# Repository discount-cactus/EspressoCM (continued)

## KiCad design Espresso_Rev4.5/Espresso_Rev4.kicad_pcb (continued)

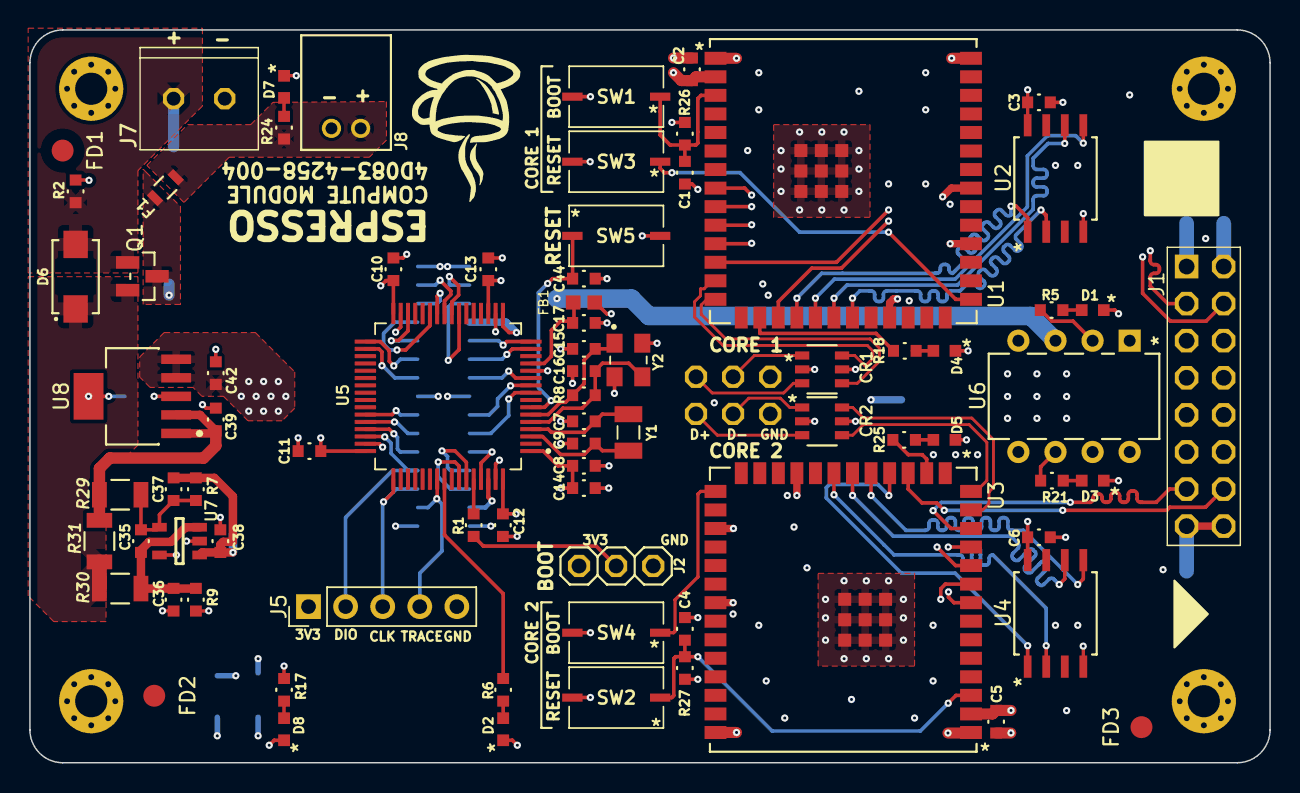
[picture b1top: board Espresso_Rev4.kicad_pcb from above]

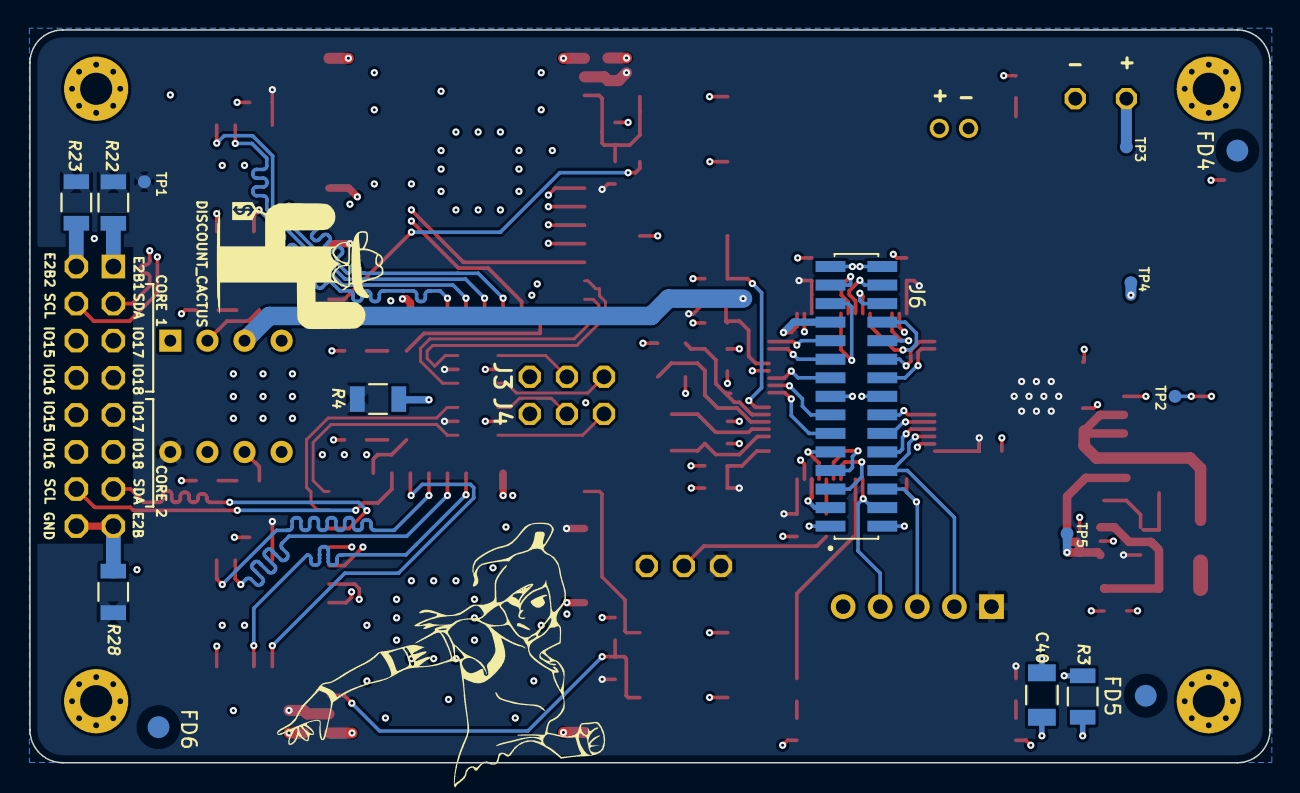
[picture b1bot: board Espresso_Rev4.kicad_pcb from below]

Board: 4 copper layers, 84.9 x 50.2 mm, 98 parts (15 on the bottom side), 89 nets.

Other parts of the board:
MH1, MH2, MH3, MH4: MountingHole_2.2mm_M2_Pad_Via

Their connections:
/SHIELD: MH1.1, MH2.1, MH3.1, MH4.1; also elsewhere on the board

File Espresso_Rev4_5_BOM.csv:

"#","Reference","Qty","Value","Footprint","Manufacturer","Part Number","Alt Part Number","Rating","Color","DNP","Voltage Rating"
"1","C14","1","4.7uF","Custom_Microcontroller:C_0603","Samsung","CL10A475MA8NQNC","","25V","","",""
"2","C40","1","4.7nF","Custom_Microcontroller:C_1206","KEMET","C1206C472KDRACAUTO","","1kV","","DNP",""
"3","C1,C4","2","1uF","Custom_Microcontroller:C_0603","Samsung","CL10A105KB8NNNC","","50V","","",""
"4","C15,C16","2","20pF","Custom_Microcontroller:C_0603","Samsung","CL10C200JB8NNNC","","50V","","",""
"5","C2,C3,C5,C6,C8,C10,C11,C12,C13,C17,C38,C44","12","100nF","Custom_Microcontroller:C_0603","Samsung","CL10B104KB8NNNC","","50V","","",""
"6","C35,C36,C37","3","220pF","Custom_Microcontroller:C_0603","Samsung","CL10B221KB8NFNC","C0603C221J5HACAUTO","50V","","",""
"7","C39,C42","2","10uF","Custom_Microcontroller:C_0603","Samsung","CL10A106MA8NRNC","","25V","","",""
"8","C7,C9","2","8pF","Custom_Microcontroller:C_0603","Samsung","CL10C080DB81PNC","","50V","","DNP",""
"9","CR1,CR2","2","USBLC6-2SC6","Custom_Microcontroller:USBLC6-2SC6","STMicroelectronics","USBLC6-2SC6","","","","",""
"10","D6","1","~","Custom_Microcontroller:SK54AHE3-LTP","MCC","SK54AHE3-LTP","","","","",""
"11","D1,D4,D5","3","~","Custom_Microcontroller:LED_0603","Lite-On Inc.","LTST-C191KGKT","","","Green","",""
"12","D2,D3,D7,D8","4","~","Custom_Microcontroller:LED_0603","Lite-On Inc.","LTST-C191KFKT","","","Orange","",""
"13","F1","1","1A","Custom_Microcontroller:MF-FSMF050X-2","Bourns","MF-FSMF050X-2 ","","","","",""
"14","FB1","1","120R","Custom_Microcontroller:FB_0603","Murata","BLM18KG121TN1D","","","","",""
"15","J1","1","~","Custom_Microcontroller:2X8","Sullins","PPTC082LJBN-RC","","","","",""
"16","J5","1","Conn_01x05","Connector_PinHeader_2.54mm:PinHeader_1x05_P2.54mm_Vertical","","","","","","",""
"17","J6","1","20021321-00030T4LF","Custom_Microcontroller:20021321-00030T4LF","Amphenol","20021321-00030T4LF","","","","",""
"18","J7","1","OSTTE020104","Custom_Microcontroller:OSTTE020104","On Shore Technology","OSTTE020104","","10A","","",""
"19","J8","1","S2B-PH-K-S","Custom_Microcontroller:S2B-PH-K-S","JST","S2B-PH-K-S","","","","",""
"20","J2,J3,J4","3","~","Custom_Microcontroller:1X3","","","","","","",""
"21","Q1","1","~","Custom_Microcontroller:DMP3099L-7","Diodes","DMP3099L-7","","","","",""
"22","R2","1","100K","Custom_Microcontroller:R_0603","Stackpole","RMCF0603FT100K","","1/10W","","",""
"23","R3","1","1M00","Custom_Microcontroller:R_1206","Stackpole","RMCF1206FG1M00","","1/4W","","DNP",""
"24","R8","1","1M00","Custom_Microcontroller:R_0603","Stackpole","RMCF0603FT1M00","","1/10W","","",""
"25","R31","1","3mOhm","Custom_Microcontroller:R_1206","Rohm Semiconductor","PMR18EZPFV3L00","","1W","","",""
"26","R1,R26,R27","3","10K","Custom_Microcontroller:R_0603","Stackpole","RMCF0603FT10K0","","1/10W","","",""
"27","R29,R30","2","97R6","Custom_Microcontroller:R_1206","KOA Speer","RK73H2BTTD97R6F","","1/4W","","",""
"28","R4,R22,R23,R28","4","4K7","Custom_Microcontroller:R_1206","Stackpole","RMCF1206FT4K70","","1/4W","","",""
"29","R5,R6,R17,R18,R21,R24,R25","7","1K","Custom_Microcontroller:R_0603","Stackpole","RMCF0603FT1K00","","1/10W","","",""
"30","R7,R9","2","73K2","Custom_Microcontroller:R_0603","Stackpole","RMCF0603FT73K2","","1/10W","","",""
"31","SW1,SW2,SW3,SW4,SW5","5","~","Custom_Microcontroller:PTS636 SK25J SMTR LFS","C&K","PTS636SK25JSMTR LFS","","","","",""
"32","U5","1","STM32F107RCT6TR","Custom_Microcontroller:STM32F107RCT6TR","STMicroelectronics","STM32F107RCT6TR","","","","",""
"33","U6","1","ATTINY85-20PU","Custom_Microcontroller:ATTINY85-20PU","Microchip","ATTINY85-20PU","","","","",""
"34","U7","1","INA180A2QDBVRQ1","Custom_Microcontroller:INA180A2QDBVRQ1","Texas Instruments","INA180A2QDBVRQ1","","","","",""
"35","U8","1","TPS7A4533DCQR","Custom_Microcontroller:TPS7A4533DCQR","Texas Instruments","TPS7A4533DCQR","","","","",""
"36","U1,U3","2","ESP32-S3-WROOM-1U-N8R2","Custom_Microcontroller:ESP32-S3-WROOM-1U-N8R2","Espressiff","ESP32-S3-WROOM-1U-N8R2","","","","",""
"37","U2,U4","2","~","Custom_Microcontroller:W25Q128JVSIQ","Winbond","W25Q128JVSIQ","","","","",""
"38","Y1","1","32.768 kHz","Custom_Microcontroller:ECS-.327-9-34B-TR","ECS","ECS-.327-9-34B-TR","","","","DNP",""
"39","Y2","1","25MHz","Custom_Microcontroller:ECS-2333-250-BN-TR","ECS","ECS-2333-250-BN-TR","","","","",""

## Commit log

2024-08-28 Initial KiCad project upload
2024-08-30 Updated BOM
    Corrected part number for 4.7 kohm resistor
2024-08-30 Removed unused schematic file
2025-05-11 Updated fab files
2025-08-02 Updated files
